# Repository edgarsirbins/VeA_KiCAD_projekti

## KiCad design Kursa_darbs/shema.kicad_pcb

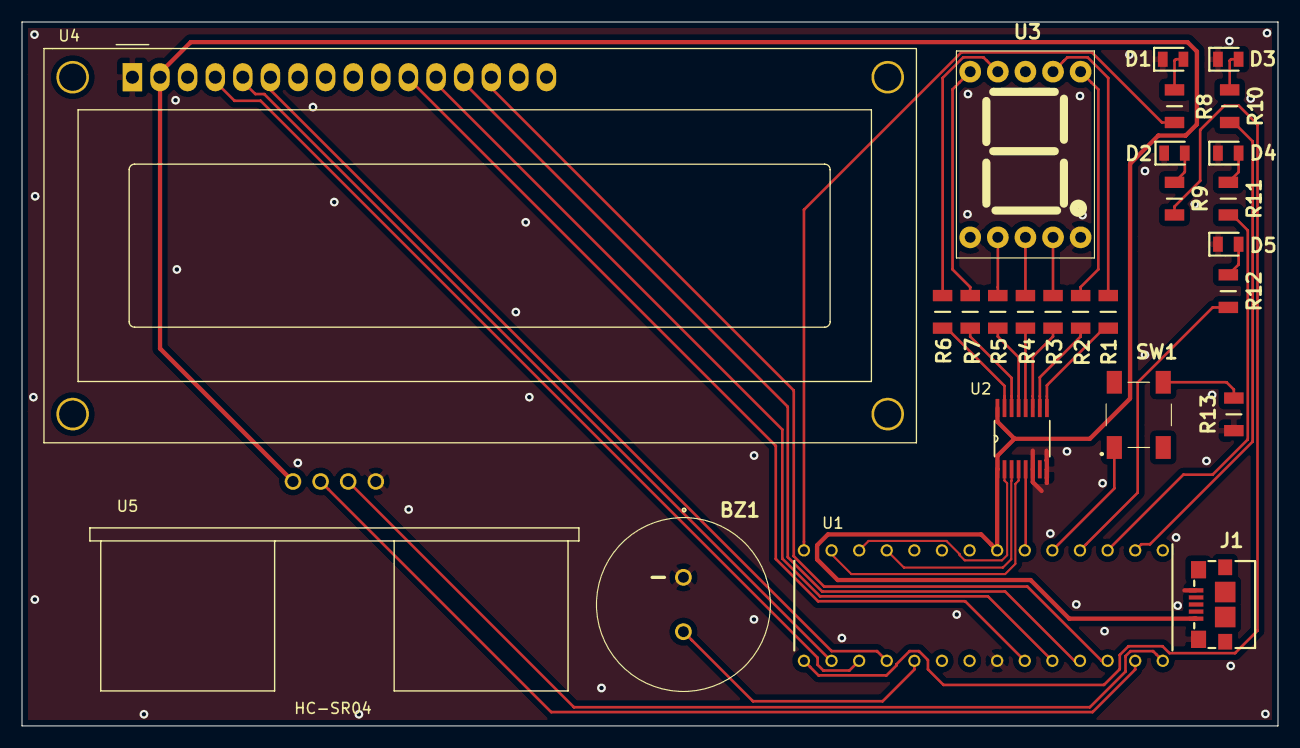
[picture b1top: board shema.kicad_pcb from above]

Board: 2 copper layers, 115.6 x 64.8 mm, 26 parts (0 on the bottom side), 42 nets.

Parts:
BZ1: SDC1610M5; SDC1610M5-01
D1, D3: Red LED; LEDC2012X90N
D2, D5: Green LED; LEDC2012X90N
D4: Yellow LED; LEDC2012X90N
J1: USB_B_Micro; 1981568-1
R1, R2, R3, R4, R5, R6, R7: 331; RESC3216X60N
R8, R9, R10, R11, R12: 102; RESC3216X60N
R13: 103; RESC3216X60N
SW1: Button; LL3301BF065QJ
U1: ATmega328P-PU; DIP1016W53P254L3468H457Q28N
U2: CD4543BPWR; CD4543B_PW_16
U3: SC56-11EWA
U4: REC001602AWPP5N00000
U5: HC-SR04; XCVR_HC-SR04

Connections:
+5V: J1.1, U1.7, U2.1, U2.16, U4.2, U5.1
/PB0: R8.2, U1.14
/PB1: R9.2, U1.15
/PB2: U1.16, U4.5
/PB3: U1.17, U4.4
/PB4: U1.18, U4.6
/PC0: U1.23, U4.11
/PC1: U1.24, U4.12
/PC2: U1.25, U4.13
/PC3: U1.26, U4.14
/PC4: U1.27, U5.2
/PC5: U1.28, U5.3
/PD0: R10.2, U1.2
/PD1: R11.2, U1.3
/PD2: R12.2, U1.4
GND: BZ1.1, D1.1, D2.1, D3.1, D4.1, D5.1, J1.5, J1.6, R13.1, U1.8, U1.22, U2.6, U2.8, U3.1, U3.5, U4.1, U5.4
unnamed: BZ1.2, U1.19
unnamed: D1.2, R8.1
unnamed: D2.2, R9.1
unnamed: D3.2, R10.1
unnamed: D4.2, R11.1
unnamed: D5.2, R12.1
unnamed: R1.1, U3.7
unnamed: R1.2, U2.9
unnamed: R2.1, U3.6
unnamed: R2.2, U2.10
unnamed: R3.1, U3.4
unnamed: R3.2, U2.11
unnamed: R4.1, U3.3
unnamed: R4.2, U2.12
unnamed: R5.1, U3.2
unnamed: R5.2, U2.13
unnamed: R6.1, U3.9
unnamed: R6.2, U2.15
unnamed: R7.1, U3.10
unnamed: R7.2, U2.14
unnamed: R13.2, SW1.4
unnamed: SW1.1, U1.5
unnamed: U1.6, U2.5
unnamed: U1.11, U2.3
unnamed: U1.12, U2.2
unnamed: U1.13, U2.4

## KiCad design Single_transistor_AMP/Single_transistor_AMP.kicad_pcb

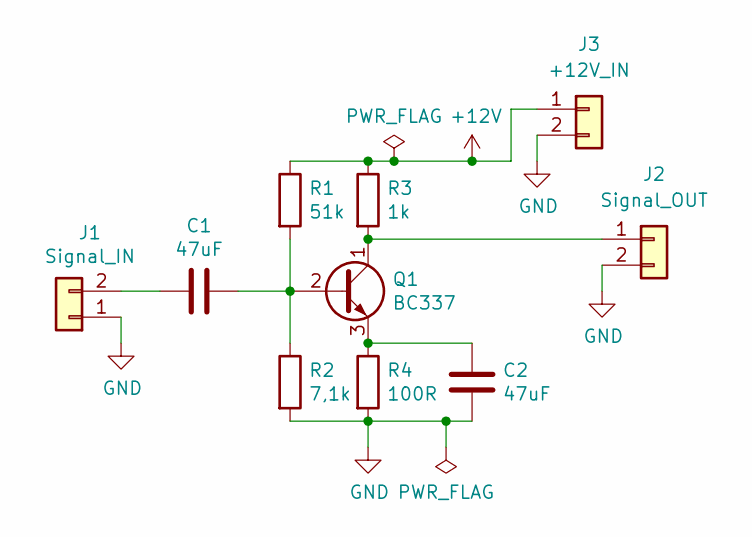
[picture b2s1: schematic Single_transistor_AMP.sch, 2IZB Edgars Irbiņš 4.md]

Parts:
C1: 47uF; CAPC1608X120N
C2: 47uF; CAPPRD250W55D630H600
J1: Signal_IN; SHDR2W90P0X508_1X2_1016X950X1500P_Conn
J2: Signal_OUT; SHDR2W90P0X508_1X2_1016X950X1500P_Conn
J3: +12V_IN; SHDR2W90P0X508_1X2_1016X950X1500P_Conn
Q1: BC337; Pkg_TO_SOT_THT-TO-92_Inline
R1: 51k; R_2512_6332Metric
R2: 7,1k; R_2010_5025Metric
R3: 1k; R_1218_3246Metric
R4: 100R; R_2512_6332Metric

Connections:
+12V: J3.1, R1.1, R3.1
GND: C2.1, J1.1, J2.2, J3.2, R2.2, R4.2
unnamed: C1.1, Q1.2 (B), R1.2, R2.1
unnamed: C1.2, J1.2
unnamed: C2.2, Q1.3 (E), R4.1
unnamed: J2.1, Q1.1 (C), R3.2

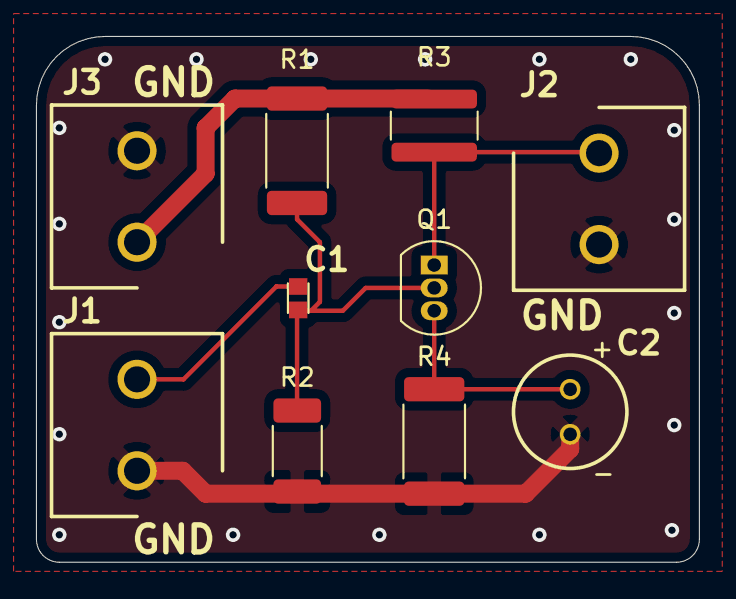
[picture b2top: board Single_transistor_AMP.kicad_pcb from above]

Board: 2 copper layers, 36.8 x 29.2 mm, 10 parts (0 on the bottom side), 6 nets.

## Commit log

2019-02-21 Tika rediģēta README.md datne, papildus informācijas sniegšanai
2019-03-06 Pievienots 3. lekcijā izstrādātais MultiVib projekts
2019-03-06 Tika izveidota jauna bibliotēka, kas satur pašizveidoto elektrisko komponenti (tranzistoru) BC846BS. Iepriekš pievienotā MultiVib shēma uzlabota, divus Tranzistorus aizvietojot ar jaunizveidoto mikro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
2019-03-06 Nācās izdzēst failus, lai uztaisītu sakarīgus komentārus
2019-03-06 Izveidots jauns simbols (BC846BS)
2019-03-06 Izveidota jauna biblioteka, ar BC846BS komponenti
2019-03-06 Kas to lai zin kam šī datne domāta...
2019-03-06 Uzlabota MultiVib shēma, aizvietojot 2 tranzistorus ar vienu IC
2019-03-07 Iesākts PWR_Supply projekts (vienkāršs barošanas bloks)
2019-03-07 Izveidoti 5 bloki un iesākts darbs ar 220v bloku
2019-03-14 Iesākts Single_transistor_AMP projekts (pastiprinātājs)
2019-03-21 Pabeigts PWR_Supply projekts (2.md)
2019-03-28 Pabeigts Single_transistor_AMP projekts (4.md)
2019-03-28 Labojums: Pievienots savienotājs +12V barošanai
2019-05-02 Pabeigts Battery treniņuzdevums
2019-05-02 Izlabots Single_transistor_AMP proj. (datulapas, footprints)
2019-05-02 Pabeigts Battery projekts/md (Papildināta Battery_Holder bibliotēka)
2019-05-02 Izlabotas sīkumainas problēmas ar footprintiem (F.Silk)
2019-05-02 Pabeigts 7.lekcijas treniņuzdevums (P.Settings, L.Setup, D.Rules)
2019-05-07 Papildināts Single_transistor_AMP projekts, pēc 8.lekcijas m.d. nosacījumiem (darbs ar Pcbnew)
2019-05-07 Pabeigts 9.lekcijā norādītais mājasdarbs
2019-05-07 Pabeigts 10.lekcijas m.d. (iegūti Gerber faili)
2019-05-08 Pabeigts 12.lekcijas m.d. (BOM un SVG datnes)
2019-05-15 Pabeigts komponenšu mājas darbs
2019-06-11 Iesākta kursa darba izstrāde
2019-06-12 Pievienoti footprinti un uzlabota eeschema shēma
2019-06-13 Pabeigts kursa darbs
2019-06-14 Pabeigta prezentācija un nelieli uzlabojumi KiCad datnēm
2019-06-14 Pievienots PDF BOM datne (Mouser)
